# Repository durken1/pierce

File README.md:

# pierce 2.0

pierce 2.0 is a split modular wireless / semi-wireless 36 key column staggered keyboard. The design is inspired by [Corne](https://github.com/foostan/crkbd) with more pinky stagger as well as only using 1u keycaps.
It is possible to build a wireless version or a semi wireless version. If building the wireless version an additional reciever dongle is required. 
In the semi wireless version the wired half is also acting as a reciever for the wireless half.
Both versions have full [QMK support](https://github.com/qmk/qmk_firmware/tree/master/keyboards/pierce).  
Supported switches: MX, Choc V1, Alps

The semi wireless version has a built in reset circuit for connecting a PS/2 pointing device.

There are 3 different PCBs: wireless (reversible), wired (right) and reciever.

A programmer is necessary to flash the wireless modules. A cheap option is getting an ST-Link V2 clone from ebay.

# Bill of materials
## Wireless
| Qty | Item                                          | Comments                                            |
|----:|-----------------------------------------------|-----------------------------------------------------|
|   2 | Pierce 2.0 wireless PCB                       |                                                     |
|   1 | Pierce 2.0 reciever PCB                       |                                                     |
|   1 | Pro micro or equivalent                       |                                                     |
|   2 | Keystone 3034 Coin cell battery retainer      | SMD                                                 |
|   2 | 2032 3.3V Coin cell battery                   |                                                     |
|   3 | YJ-14015 / Core51822 (B)                      |                                                     |
|   3 | 1x4 pin Right-angle 2.54 mm header            | For programming RF modulules. Optional, temporary soldered wires works fine|
|   2 | 4.7 kΩ resistor                               | SMD 1206                                            |
|   1 | 1117 3.3 V regulator                          | SMD SOT-223                                         |
|   1 | THT momentary switch                          | 2 pin THT 6 mm                                      |
  
## Semi wireless
| Qty | Item                                          | Comments                                            |
|----:|-----------------------------------------------|-----------------------------------------------------|
|   1 | Pierce 2.0 wireless PCB                       |                                                     |
|   1 | Pierce 2.0 wired PCB                          |                                                     |
|   1 | Pro micro or equivalent                       | Elite C recommended if using trackpoint. (Pin D5 broken out)|
|   1 | Keystone 3034 Coin cell battery retainer      | SMD                                                 |
|   1 | 2032 3.3V Coin cell battery                   |                                                     |
|   2 | YJ-14015 / Core51822 (B)                      |                                                     |
|   2 | 1x4 pin Right-angle 2.54 mm header            | For programming RF modulules. Optional, temporary soldered wires works fine|
| 2/4 | 4.7 kΩ resistor                               | SMD 1206, 4 if using trackpoint, otherwise 2        |
|   1 | 1117 3.3 V regulator                          | SMD SOT-223                                         |
|   1 | THT momentary switch                          | 2 pin THT 6 mm                                      |
|   1 | 100 kΩ resistor                               | SMD 1206 Only for trackpoint                        |
|   1 | 2.2 uF capacitor                              | SMD 1206 Only for trackpoint                        |
|   1 | Trackpoint module                             | [R61](https://deskthority.net/wiki/TrackPoint_Hardware#ThinkPad_R61_TrackPoint) recommended, Only for.. well..|
  
# Build instructions
## Soldering

The soldering is pretty straight forward and it should be obvious what component goes where. If you haven't soldered SMD components before I recommend watching a youtube tutorial or two beforehand. I suggest adding a bit of solder to the middle pad for the battery holder.

## Flashing wireless modules

The following instructions is for using an ST-Link V2 clone and Windows.
1. Download and install OpenOCD from https://openocd.org/ and drivers for the programmer from https://www.st.com/en/development-tools/stsw-link009.html
2. Create a file called 'openocd.cfg' in the bin folder where you installed OpenOCD with the following content:

        #nRF51822 Target
        source [find interface/stlink-v2.cfg]

        transport select hla_swd

        set WORKAREASIZE 0x4000
        source [find target/nrf51.cfg]

3. Copy the relevant firmware .bin file to the bin folder where you installed OpenOCD
4. Connect the 4 pins SWCLK, SWDIO, GND and 3.3 V on the ST-Link V2 to the matching pad on the PCB and the ST-Link to the computer
5. Open a command prompt, navigate to the bin folder mentioned above and enter:

        openocd.exe -f openocd.cfg
        
6. Open another command prompt and enter:

        telnet localhost 4444
You should now be connected to the programmer. Enter the following commands to flash the firmware:

    halt
    nrf51 mass_erase
    program <firmware_file_name>.bin
    reset

That's it! You should now have a working pierce keyboard.

# Plates
## These need some work
I have included files to 3D print bottom plates and switch plates (only for alps for now). The idea of the screwless bottom plates is to use a friction fit, but I'm not sure how well the current version fits.

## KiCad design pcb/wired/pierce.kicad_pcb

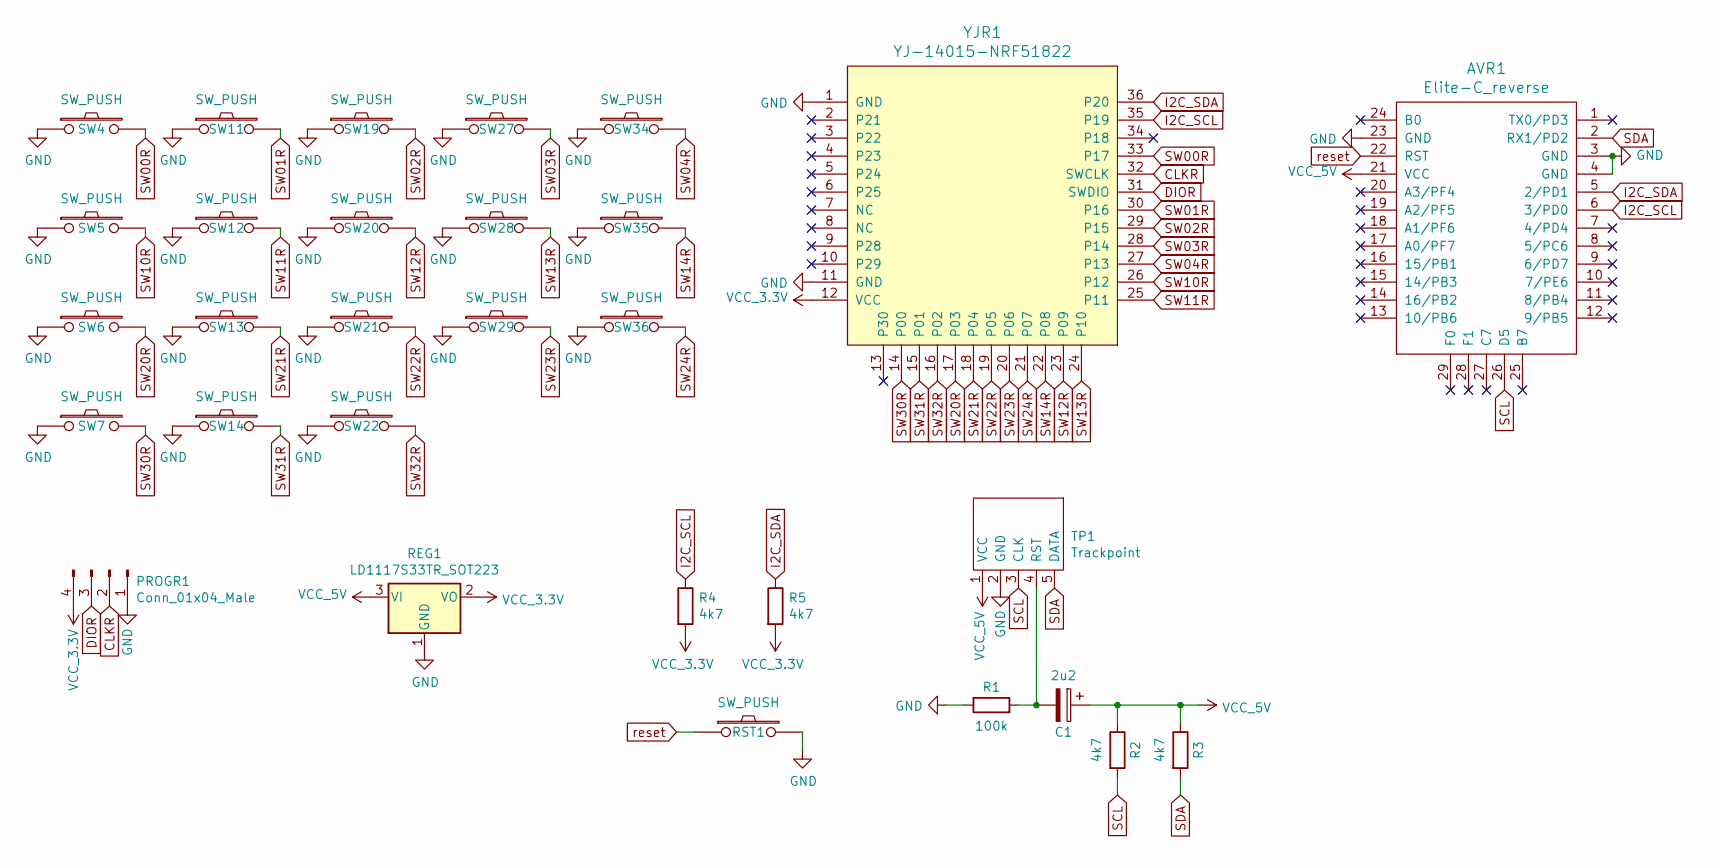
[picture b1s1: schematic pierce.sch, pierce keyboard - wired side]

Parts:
AVR1: Elite-C_reverse; Elite-C_reverse_D5
C1: 2u2; C_SMD_v2
PROGR1: Conn_01x04_Male; PinHeader_1x04_P2.54mm_Horizontal
R1: 100k; R_SMD_v2
R2, R3, R4, R5: 4k7; R_SMD_v2
REG1: LD1117S33TR_SOT223; SOT-223-3_TabPin2
RST1: SW_PUSH; ResetSW_1side
SW4, SW5, SW6, SW7, SW11, SW12, SW13, SW14, SW19, SW20, SW21, SW22, SW27, SW28, SW29, SW34, SW35, SW36: SW_PUSH; CherryMX_ChocV2_1u
TP1: Trackpoint; TRACKPOINT
YJR1: YJ-14015-NRF51822; YJ-14015

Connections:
CLKR: PROGR1.2, YJR1.32 (SWCLK)
DIOR: PROGR1.3, YJR1.31 (SWDIO)
GND: AVR1.3 (GND), AVR1.4 (GND), AVR1.23 (GND), PROGR1.1, R1.1, REG1.1 (GND), RST1.2, SW4.1, SW5.1, SW6.1, SW7.1, SW11.1, SW12.1, SW13.1, SW14.1, SW19.1, SW20.1, SW21.1, SW22.1, SW27.1, SW28.1, SW29.1, SW34.1, SW35.1, SW36.1, TP1.2 (GND), YJR1.1 (GND), YJR1.11 (GND)
I2C_SCL: AVR1.6 (3/PD0), R4.1, YJR1.35 (P19)
I2C_SDA: AVR1.5 (2/PD1), R5.1, YJR1.36 (P20)
unnamed: C1.2, R1.2, TP1.4 (RST)
SCL: AVR1.26 (D5), R2.2, TP1.3 (CLK)
SDA: AVR1.2 (RX1/PD2), R3.2, TP1.5 (DATA)
SW00R: SW4.2, YJR1.33 (P17)
SW01R: SW11.2, YJR1.30 (P16)
SW02R: SW19.2, YJR1.29 (P15)
SW03R: SW27.2, YJR1.28 (P14)
SW04R: SW34.2, YJR1.27 (P13)
SW10R: SW5.2, YJR1.26 (P12)
SW11R: SW12.2, YJR1.25 (P11)
SW12R: SW20.2, YJR1.23 (P09)
SW13R: SW28.2, YJR1.24 (P10)
SW14R: SW35.2, YJR1.22 (P08)
SW20R: SW6.2, YJR1.17 (P03)
SW21R: SW13.2, YJR1.18 (P04)
SW22R: SW21.2, YJR1.19 (P05)
SW23R: SW29.2, YJR1.20 (P06)
SW24R: SW36.2, YJR1.21 (P07)
SW30R: SW7.2, YJR1.14 (P00)
SW31R: SW14.2, YJR1.15 (P01)
SW32R: SW22.2, YJR1.16 (P02)
VCC_3.3V: PROGR1.4, R4.2, R5.2, REG1.2 (VO), YJR1.12 (VCC)
VCC_5V: AVR1.21 (VCC), C1.1, R2.1, R3.1, REG1.3 (VI), TP1.1 (VCC)
reset: AVR1.22 (RST), RST1.1

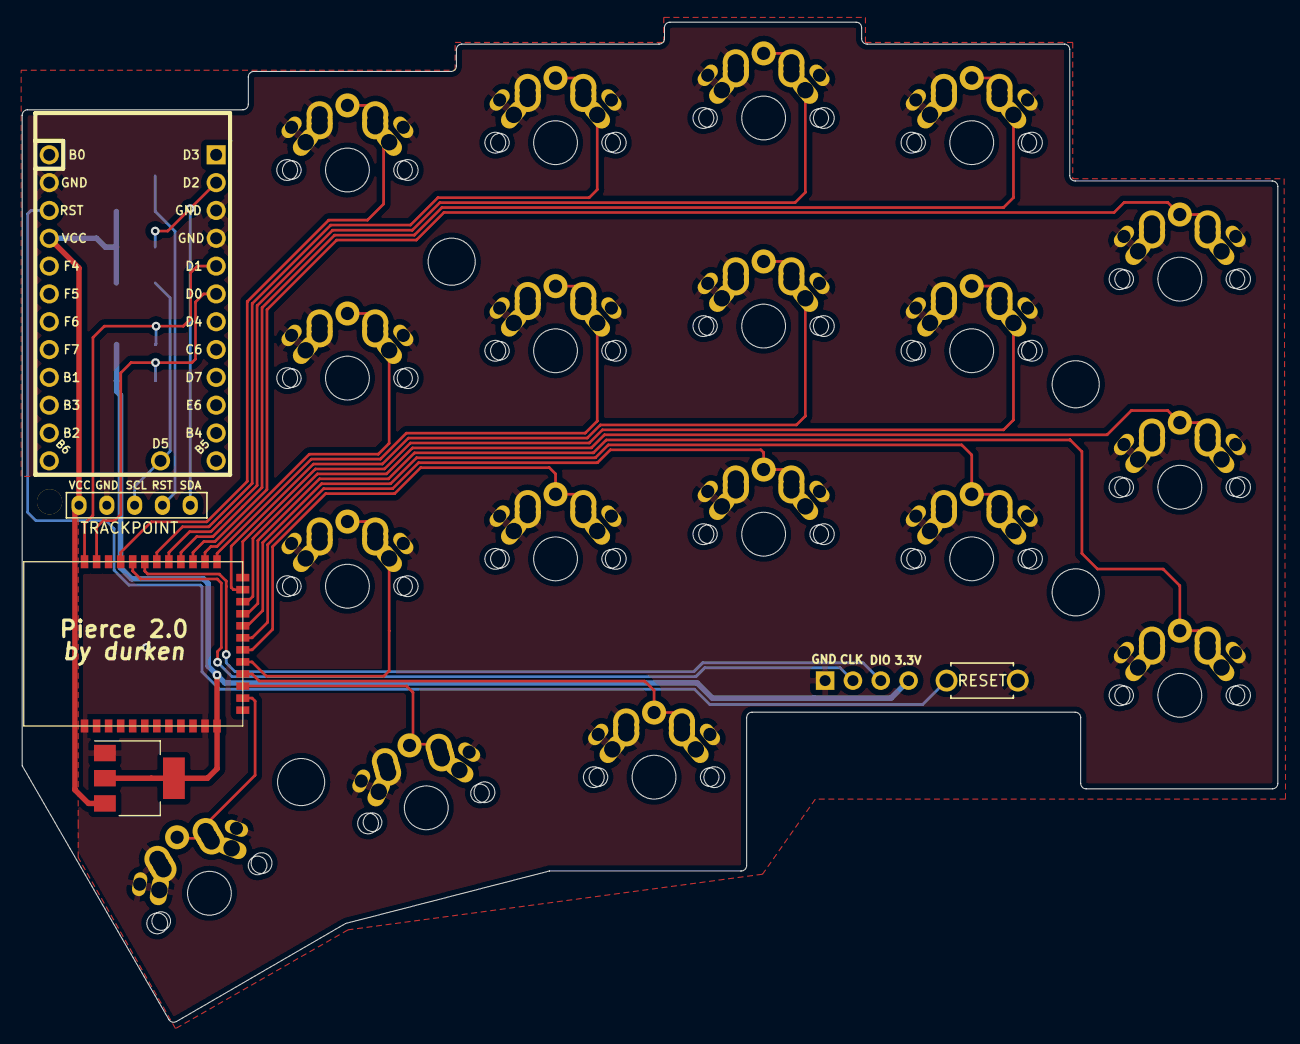
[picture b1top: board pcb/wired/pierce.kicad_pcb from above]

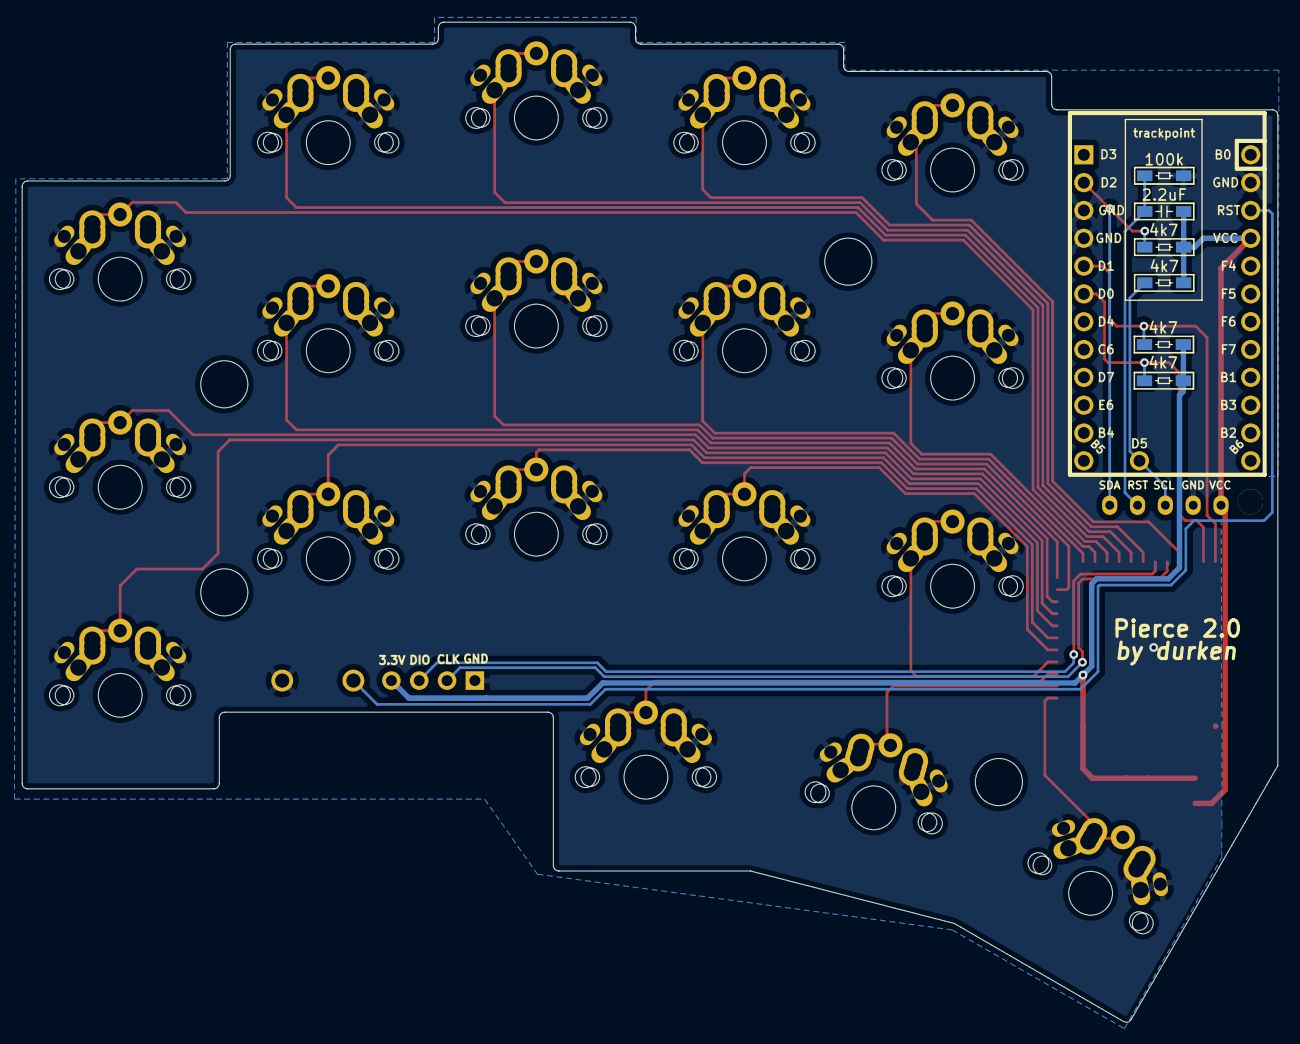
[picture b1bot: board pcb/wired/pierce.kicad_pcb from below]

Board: 2 copper layers, 114.6 x 91.3 mm, 35 parts (7 on the bottom side), 29 nets.

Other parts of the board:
Ref**: Val**; M2_HOLE_v2
Ref**#2, Ref**#3, Ref**#4: Val**; M2_HOLE_v2
Ref**#5: Val**; M2_Threads_v2

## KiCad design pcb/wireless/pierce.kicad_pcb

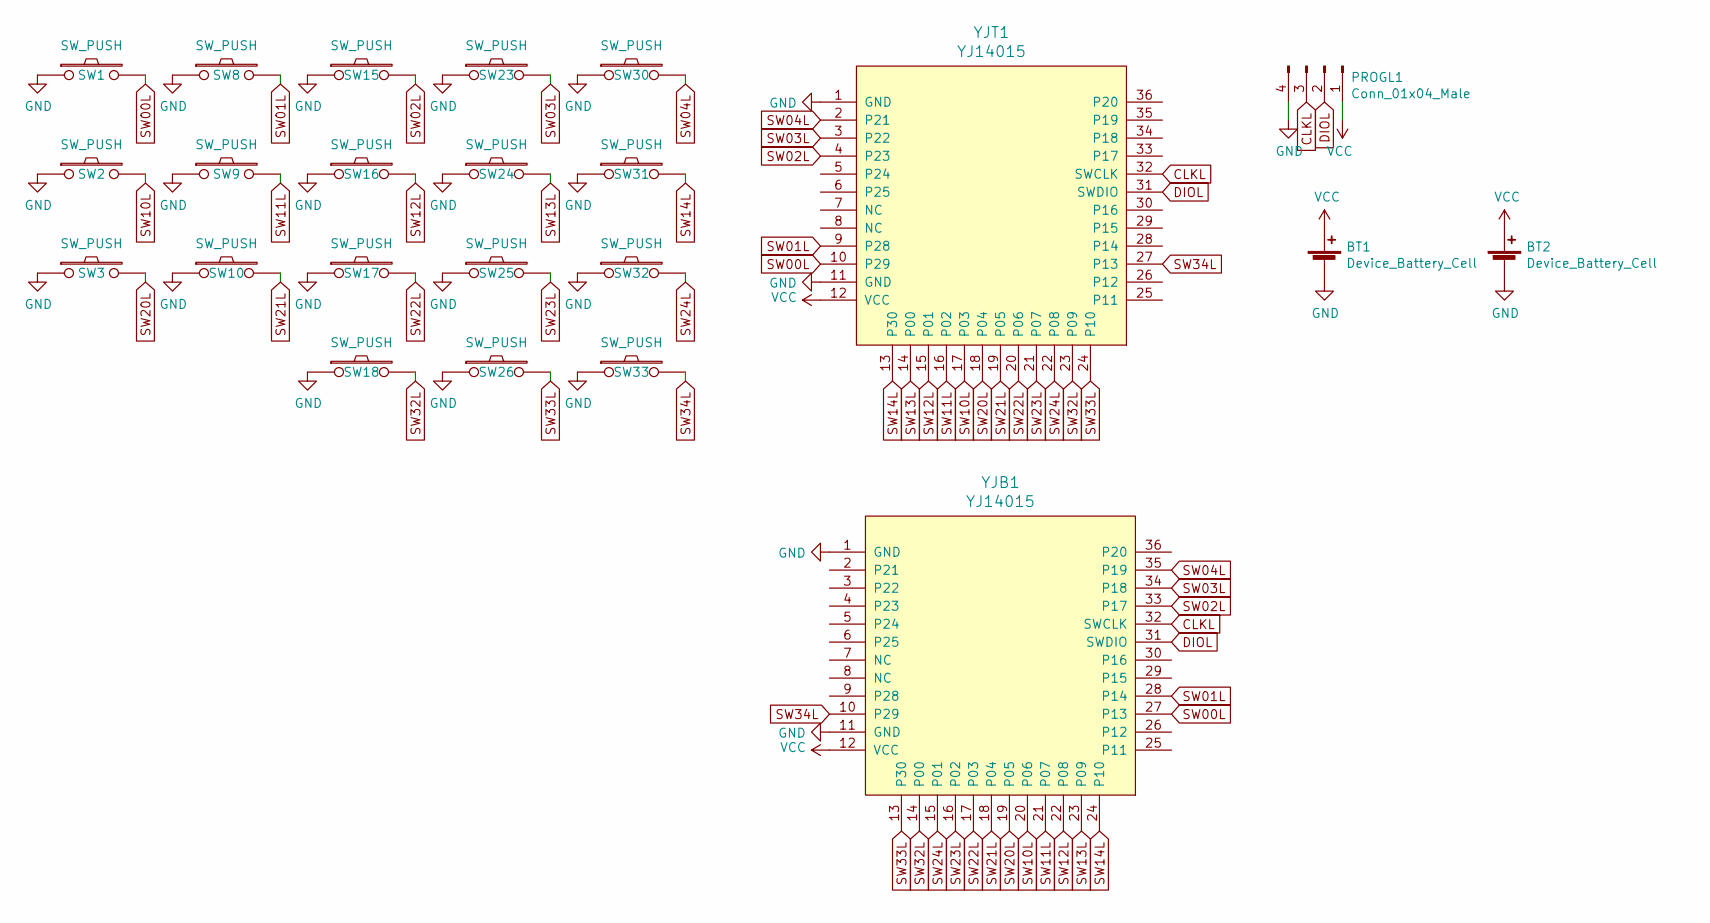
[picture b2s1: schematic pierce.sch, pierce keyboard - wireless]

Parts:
BT1, BT2: Device_Battery_Cell; BatteryHolder_Keystone_3034_1x20mm
PROGL1: Conn_01x04_Male; PinHeader_1x04_P2.54mm_Horizontal
SW1, SW2, SW3, SW8, SW9, SW10, SW15, SW16, SW17, SW18, SW23, SW24, SW25, SW26, SW30, SW31, SW32, SW33: SW_PUSH; MX_ALPS_PG1350_noLed
YJB1: YJ14015; YJ-14015
YJT1: YJ14015; YJ-14015

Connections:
CLKL: PROGL1.3, YJB1.32 (SWCLK), YJT1.32 (SWCLK)
DIOL: PROGL1.2, YJB1.31 (SWDIO), YJT1.31 (SWDIO)
GND: BT1.2 (-), BT2.2 (-), PROGL1.4, SW1.1, SW2.1, SW3.1, SW8.1, SW9.1, SW10.1, SW15.1, SW16.1, SW17.1, SW18.1, SW23.1, SW24.1, SW25.1, SW26.1, SW30.1, SW31.1, SW32.1, SW33.1, YJB1.1 (GND), YJB1.11 (GND), YJT1.1 (GND), YJT1.11 (GND)
SW00L: SW1.2, YJB1.27 (P13), YJT1.10 (P29)
SW01L: SW8.2, YJB1.28 (P14), YJT1.9 (P28)
SW02L: SW15.2, YJB1.33 (P17), YJT1.4 (P23)
SW03L: SW23.2, YJB1.34 (P18), YJT1.3 (P22)
SW04L: SW30.2, YJB1.35 (P19), YJT1.2 (P21)
SW10L: SW2.2, YJB1.20 (P06), YJT1.17 (P03)
SW11L: SW9.2, YJB1.21 (P07), YJT1.16 (P02)
SW12L: SW16.2, YJB1.22 (P08), YJT1.15 (P01)
SW13L: SW24.2, YJB1.23 (P09), YJT1.14 (P00)
SW14L: SW31.2, YJB1.24 (P10), YJT1.13 (P30)
SW20L: SW3.2, YJB1.19 (P05), YJT1.18 (P04)
SW21L: SW10.2, YJB1.18 (P04), YJT1.19 (P05)
SW22L: SW17.2, YJB1.17 (P03), YJT1.20 (P06)
SW23L: SW25.2, YJB1.16 (P02), YJT1.21 (P07)
SW24L: SW32.2, YJB1.15 (P01), YJT1.22 (P08)
SW32L: SW18.2, YJB1.14 (P00), YJT1.23 (P09)
SW33L: SW26.2, YJB1.13 (P30), YJT1.24 (P10)
SW34L: SW33.2, YJB1.10 (P29), YJT1.27 (P13)
VCC: BT1.1 (+), BT2.1 (+), PROGL1.1, YJB1.12 (VCC), YJT1.12 (VCC)

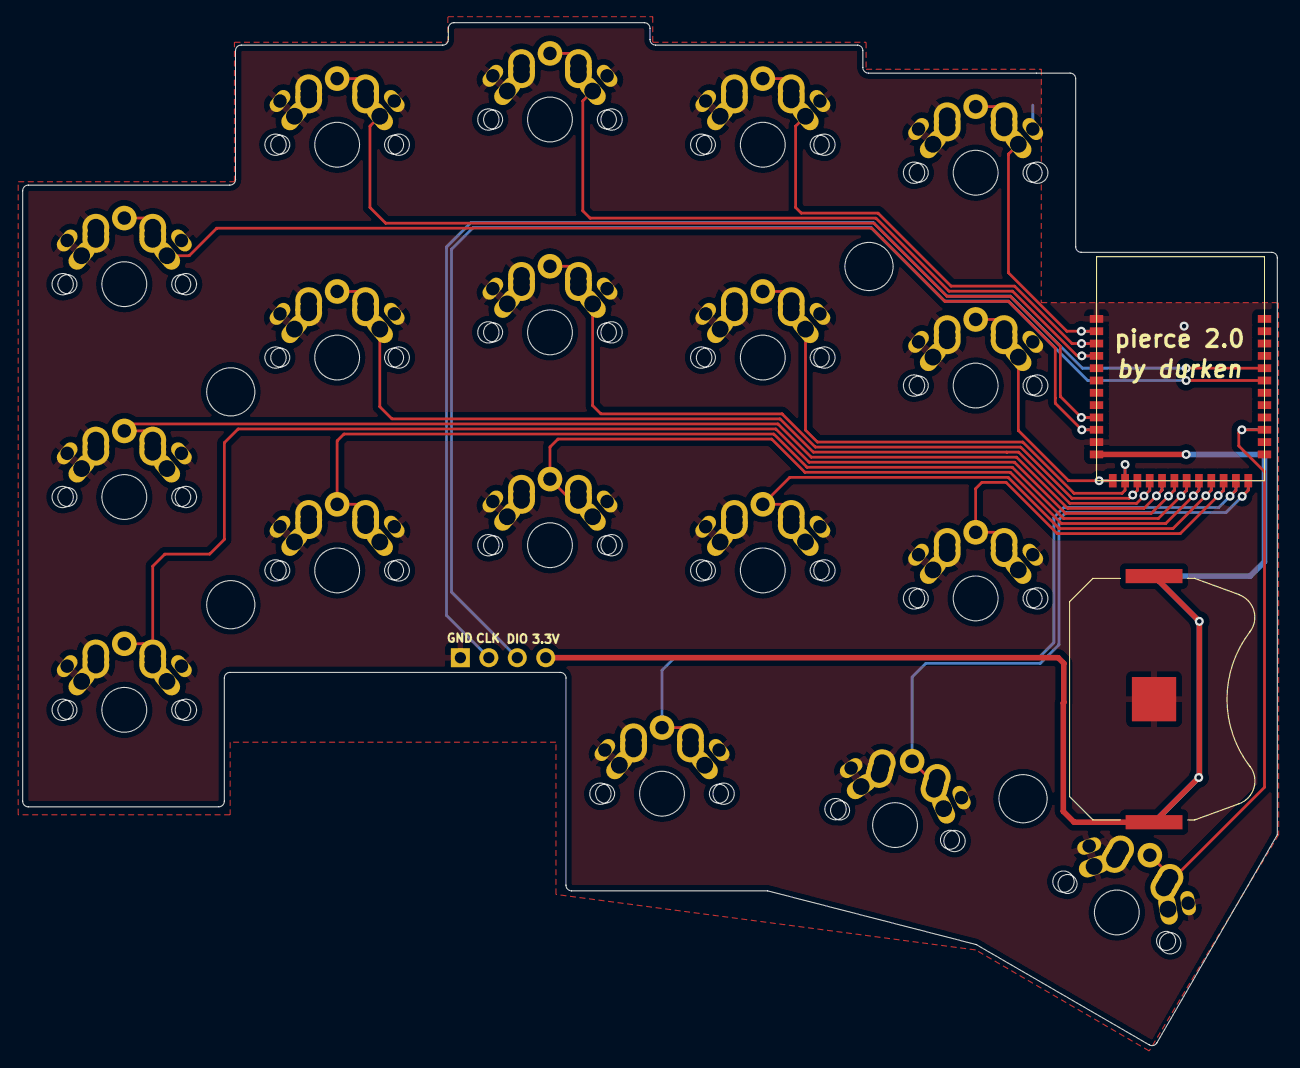
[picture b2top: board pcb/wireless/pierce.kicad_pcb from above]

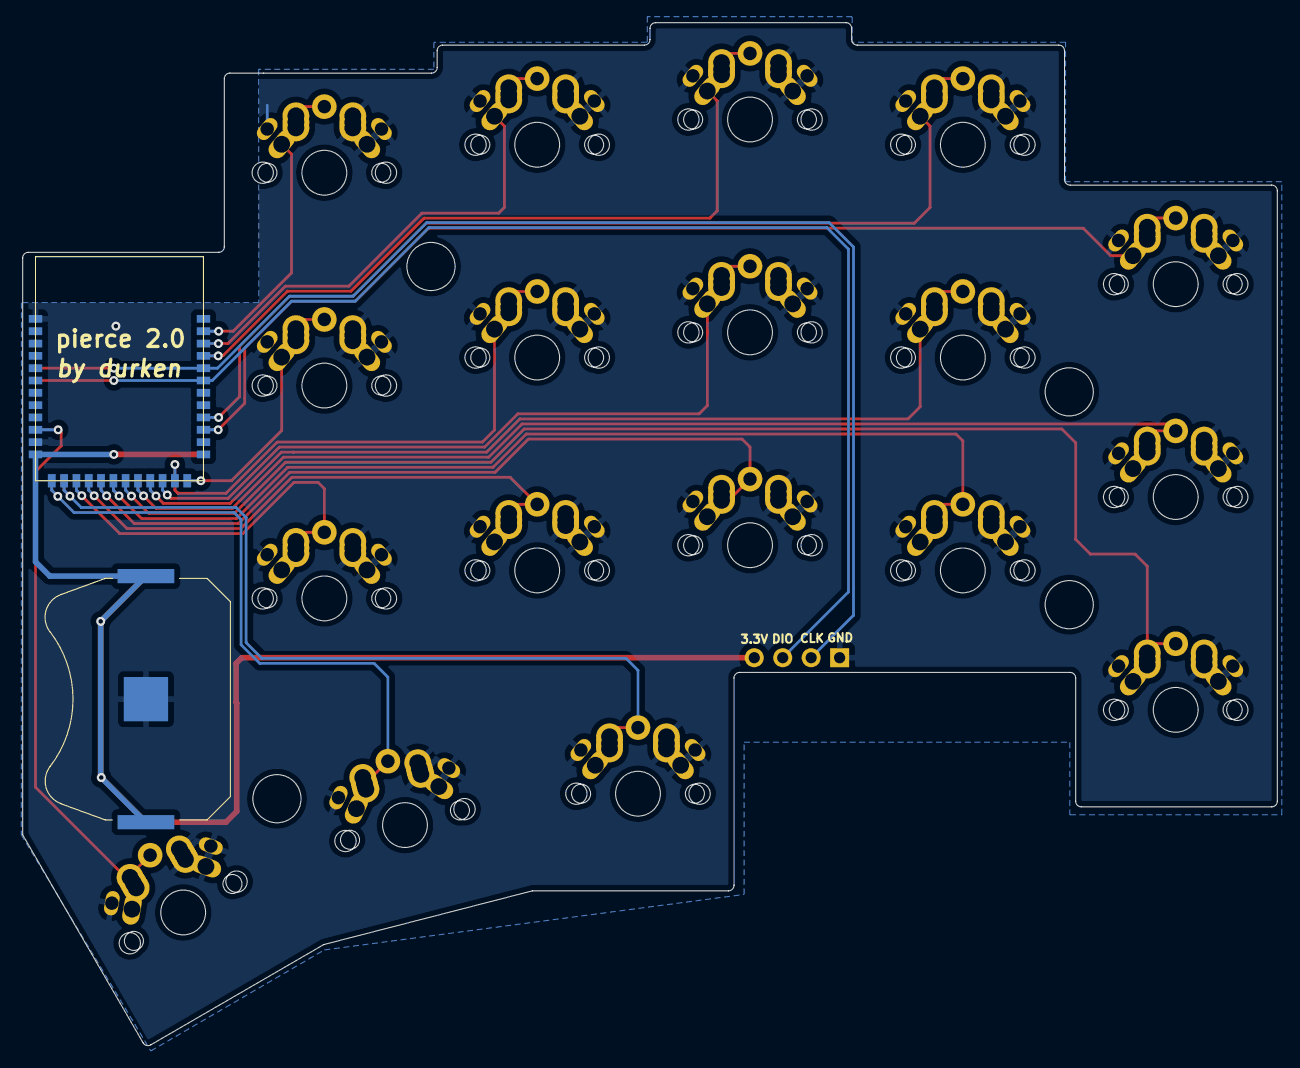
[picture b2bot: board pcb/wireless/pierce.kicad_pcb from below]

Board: 2 copper layers, 112.0 x 91.3 mm, 27 parts (2 on the bottom side), 22 nets.

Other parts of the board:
Ref**: Val**; M2_HOLE_v2
Ref**#2, Ref**#3, Ref**#4: Val**; M2_HOLE_v2

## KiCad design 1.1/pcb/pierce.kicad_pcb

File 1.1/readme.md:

# pierce keyboard

* Based on crkbd
* Soldered Cherry MX / Kailh choc / alps
* Using one MCU and an IDC connection between halves
* Trackpoint connection including reset circuit
* Split 3x5+3 column stagger

# Bill of materials
| Qty | Item                                          | Notes                                               |
|----:|-----------------------------------------------|-----------------------------------------------------|
|   1 | Pierce left PCB                               |                                                     |
|   1 | Pierce right PCB                              |                                                     |
|  36 | Diodes                                        | 1N4148W or similar SOD-123                          |
|  36 | Switches                                      | MX, Choc V1 or alps                                 |
|   1 | Microcontroller                               | Elite-c recommended if using trackpoint             |
|   2 | Angled 12 pin IDC connector                   | [Example](https://www.conrad.com/p/tru-components-1589771-pin-connector-no-ejector-contact-spacing-254-mm-total-number-of-pins-12-no-of-rows-2-1-pcs-1589771)|
|   2 | 12 pin IDC pin connector                      | [Example](https://www.conrad.com/p/bkl-electronic-10120991-pin-connector-strain-relief-contact-spacing-254-mm-total-number-of-pins-12-no-of-rows-2-1-2103795)|
|   1 | 12 connector ribbon cable                     | [Example](https://www.conrad.com/p/lapp-49900055-ribbon-cable-contact-spacing-127-mm-14-x-009-mm-grey-sold-per-metre-609735)|
|   1 | 6.5 mm reset switch                           | [Example](https://www.conrad.com/p/tru-components-yst-1101-pushbutton-12-v-dc-005-a-1-x-offon-momentary-1-pcs-1569015)|

If using trackpoint:

| Qty | Item                                          | Notes                                               |
|----:|-----------------------------------------------|-----------------------------------------------------|
|   1 | Trackpoint module                             | [R61](https://deskthority.net/wiki/TrackPoint_Hardware) recommended|
|   1 | 100 kOhm resistor                             | SMD 1206                                                    |
|   2 | 4.7 kOhm resistor                             | SMD 1206                                                    |
|   1 | 2.2 uF capacitor                              | SMD 1206                                                    |

For 3D-printed case:
| Qty | Item                                          | Notes                                               |
|----:|-----------------------------------------------|-----------------------------------------------------|
|  10 | 6mm M2 spacer                                 |                                                     |
|  20 | 6mm M2 screw                                  | Countersunk recommended                             |

[Firmware](https://github.com/durken1/qmk_firmware/tree/pierce/keyboards/pierce)

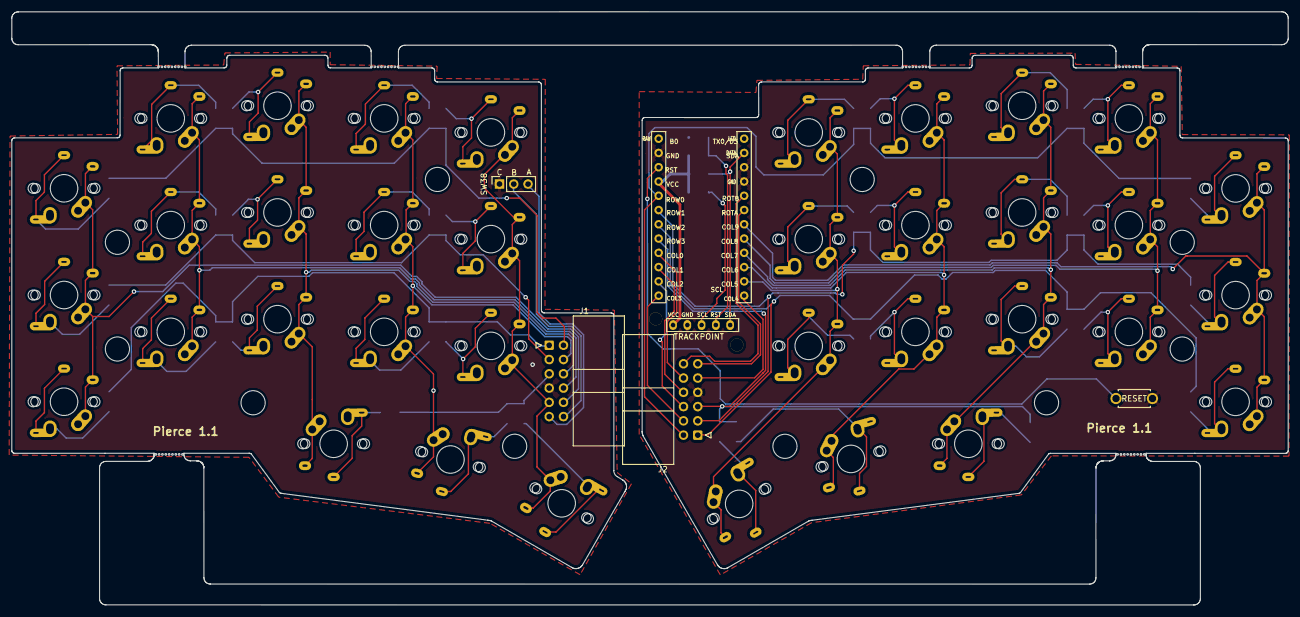
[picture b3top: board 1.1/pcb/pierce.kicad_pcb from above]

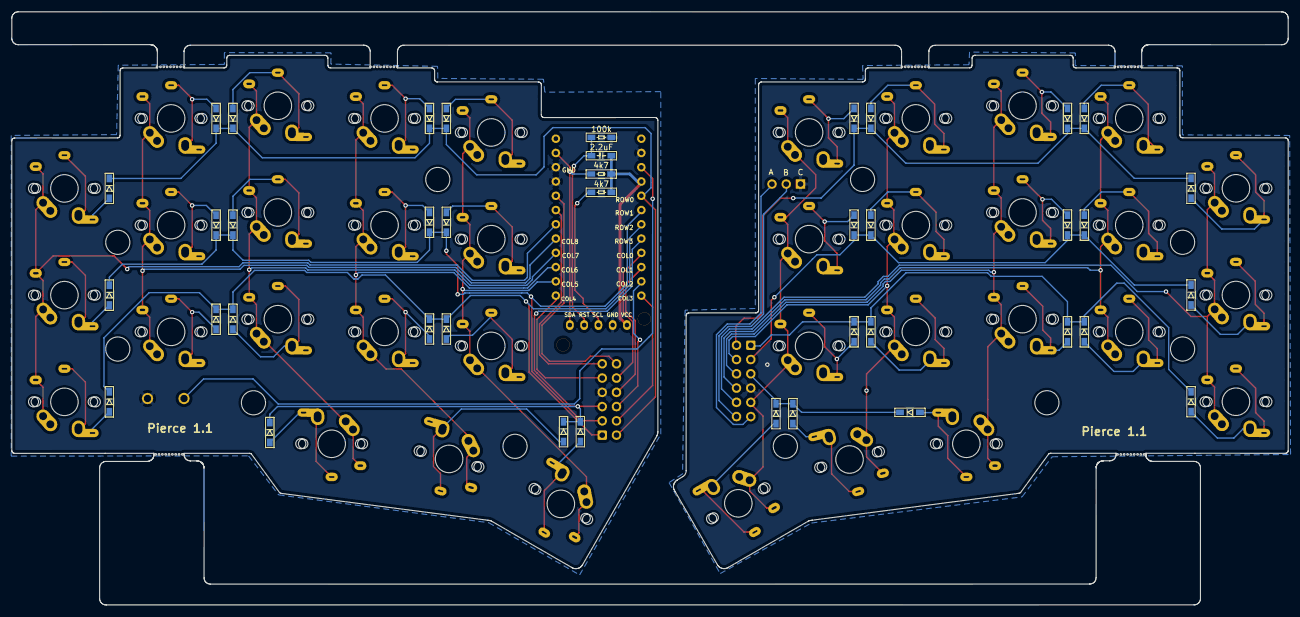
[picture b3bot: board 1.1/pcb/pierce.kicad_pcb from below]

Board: 2 copper layers, 227.3 x 105.6 mm, 94 parts (40 on the bottom side), 70 nets.

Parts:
C1: 2u2; C_SMD_v2
D1, D2, D3, D4, D5, D6, D7, D8, D9, D10, D11, D12, D13, D14, D15, D16, D17, D18, D19, D20, D21, D22, D23, D24, D25, D26, D27, D28, D29, D30, D31, D32, D33, D34, D35, D36: D; D3_SMD_v2
J1, J2: Conn_01x12; IDC-Header_2x06_P2.54mm_Horizontal
J3: Trackpoint; TRACKPOINT
R1: 100k; R_SMD_v2
R2, R3: 4k7; R_SMD_v2
Ref**: Val**; M2_HOLE_v2
Ref**#2, Ref**#3, Ref**#4, Ref**#5, Ref**#6, Ref**#7, Ref**#8, Ref**#9, Ref**#10: Val**; M2_HOLE_v2
Ref**#11, Ref**#12: Val**; M2_Threads_v2
SW1, SW2, SW3, SW4, SW5, SW6, SW7, SW8, SW9, SW10, SW11, SW12, SW13, SW14, SW15, SW16, SW17, SW18, SW19, SW20, SW21, SW22, SW23, SW24, SW25, SW26, SW27, SW28, SW29, SW30, SW31, SW32, SW33, SW34, SW35, SW36: SW_PUSH; keyswitch_cherrymx_alps_choc12_1u
SW37: SW_PUSH; ResetSW_1side
SW38: Rotary_Encoder; Rotary_encoder_conn
U1: Elite-C_reverse; ProMicro_v2_1side

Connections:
GND: J2.7, J3.2, R1.1, SW37.2, U1.3, U1.4, U1.23
GND1: J1.7, SW38.C
unnamed: C1.2, J3.4, R1.2
unnamed: D1.2, SW1.2
unnamed: D2.2, SW2.2
unnamed: D3.2, SW3.2
unnamed: D4.2, SW4.2
unnamed: D5.2, SW5.2
unnamed: D6.2, SW6.2
unnamed: D7.2, SW7.2
unnamed: D8.2, SW8.2
unnamed: D9.2, SW9.2
unnamed: D10.2, SW10.2
unnamed: D11.2, SW11.2
unnamed: D12.2, SW12.2
unnamed: D13.2, SW13.2
unnamed: D14.2, SW14.2
unnamed: D15.2, SW15.2
unnamed: D16.2, SW16.2
unnamed: D17.2, SW17.2
unnamed: D18.2, SW18.2
unnamed: D19.2, SW19.2
unnamed: D20.2, SW20.2
unnamed: D21.2, SW21.2
unnamed: D22.2, SW22.2
unnamed: D23.2, SW23.2
unnamed: D24.2, SW24.2
unnamed: D25.2, SW25.2
unnamed: D26.2, SW26.2
unnamed: D27.2, SW27.2
unnamed: D28.2, SW28.2
unnamed: D29.2, SW29.2
unnamed: D30.2, SW30.2
unnamed: D31.2, SW31.2
unnamed: D32.2, SW32.2
unnamed: D33.2, SW33.2
unnamed: D34.2, SW34.2
unnamed: D35.2, SW35.2
unnamed: D36.2, SW36.2
SCL: J3.3, R2.2
SDA: J3.5, R3.2, U1.2
VCC: C1.1, J3.1, R2.1, R3.1, U1.21
col0: J2.10, U1.16
col0l: J1.10, SW1.1, SW2.1, SW3.1
col1: J2.8, U1.15
col1l: J1.8, SW8.1, SW9.1, SW10.1
col2: J2.6, U1.14
col2l: J1.6, SW15.1, SW16.1, SW17.1, SW18.1
col3: J2.4, U1.13
col3l: J1.4, SW23.1, SW24.1, SW25.1, SW26.1
col4: J2.9, U1.12
col4l: J1.9, SW30.1, SW31.1, SW32.1, SW33.1
col5: SW4.1, SW5.1, SW6.1, SW7.1, U1.11
col6: SW11.1, SW12.1, SW13.1, SW14.1, U1.10
col7: SW19.1, SW20.1, SW21.1, SW22.1, U1.9
col8: SW27.1, SW28.1, SW29.1, U1.8
col9: SW34.1, SW35.1, SW36.1, U1.7
reset: SW37.1, U1.22
rota: J2.11, U1.6
rotal: J1.11, SW38.A
rotb: J2.12, U1.5
rotbl: J1.12, SW38.B
row0: D4.1, D11.1, D19.1, D27.1, D34.1, J2.2, U1.20
row0l: D1.1, D8.1, D15.1, D23.1, D30.1, J1.2
row1: D5.1, D12.1, D20.1, D28.1, D35.1, J2.3, U1.19
row1l: D2.1, D9.1, D16.1, D24.1, D31.1, J1.3
row2: D6.1, D13.1, D21.1, D29.1, D36.1, J2.1, U1.18
row2l: D3.1, D10.1, D17.1, D25.1, D32.1, J1.1
row3: D7.1, D14.1, D22.1, J2.5, U1.17
row3l: D18.1, D26.1, D33.1, J1.5

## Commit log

2021-02-12 Init
2021-02-13 v 0.2
2021-02-14 Routed right half
2021-02-15 Finished routing (improved routing from last commit)
2021-02-17 Adjusted text on silk layer
2021-02-17 Create LICENSE
2021-02-17 moved pcb files to pcb folder
2021-02-17 added pcb.png
2021-02-17 edit readme
2021-02-18 Changed footprint to Elite-C (Reversed for flipped mounting) Changed pins connected to trackpoint to allow USART. (CLK-D5, SDA-D2) Rearranged connection order of trackpoint to match R61 module Cleane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
2021-02-18 update assets
2021-02-18 added back missing mounting holes
2021-02-22 added plate hole footprint
2021-02-24 added silk text
2021-02-24 add connection for rotary encoder
2021-02-24 small adjustments
2021-02-24 index on master: e8ca98d small adjustments
2021-02-24 locked mounting holes
2021-02-24 cleaning
2021-02-28 changed switch footprint to support alps switcher
2021-03-03 adjust edgecut. add breakaway tabs
2021-03-04 add seperate pcbs for left/right.
2021-03-17 change pro micro footprint, smaller drill holes
2021-03-24 add case STLs
2021-03-26 update pic
2021-05-07 add layout example
2021-05-07 update layout
2021-05-10 add media keys
2021-06-15 update readme with BOM
2021-06-16 add gerber files
2021-06-16 small schematics cleanup
2021-06-16 pcb files cleanup
2021-06-16 cleanup
2021-06-17 adjust schematics for wireless connection between halves
2021-06-17 adjust schematics with i2c connecion to elite-c
2021-06-18 place and route 2.0
2021-06-21 change footprint to make wireless side reversible
2021-06-21 add reciever pcb for dual wireless setup
2021-06-21 rearrange folder structure
2021-06-21 add pcb pics
2021-06-22 add gnd planes
2021-06-22 small visual adjustments
2021-06-23 small pcb adjustments
2021-10-19 schematic done, started place & route
2022-03-18 prototype - ordered
2022-05-11 cleanup, add wireless_modules_firmware
2022-05-21 add some plates for 3d printing
2022-09-06 Top and bottom plates for MX Cherry switches.
    Top and bottom plates for MX Cherry switches.
    They are not ideal, there are room for improvement.
    Have a nice day.
2022-10-12 Delete 20220712.DURKEN1.PIERCE.00.stl
    Can't find another way to rename.
2022-10-12 Delete 20220710.DURKEN1.PIERCE.01.stl
    Can't find another way to rename.
2022-10-12 Add files via upload
    Can't find another way to rename.
2024-01-29 Update README.md
    fix white balance in picture
2024-09-14 add reciever box stl files. thanks @tokyo2006
